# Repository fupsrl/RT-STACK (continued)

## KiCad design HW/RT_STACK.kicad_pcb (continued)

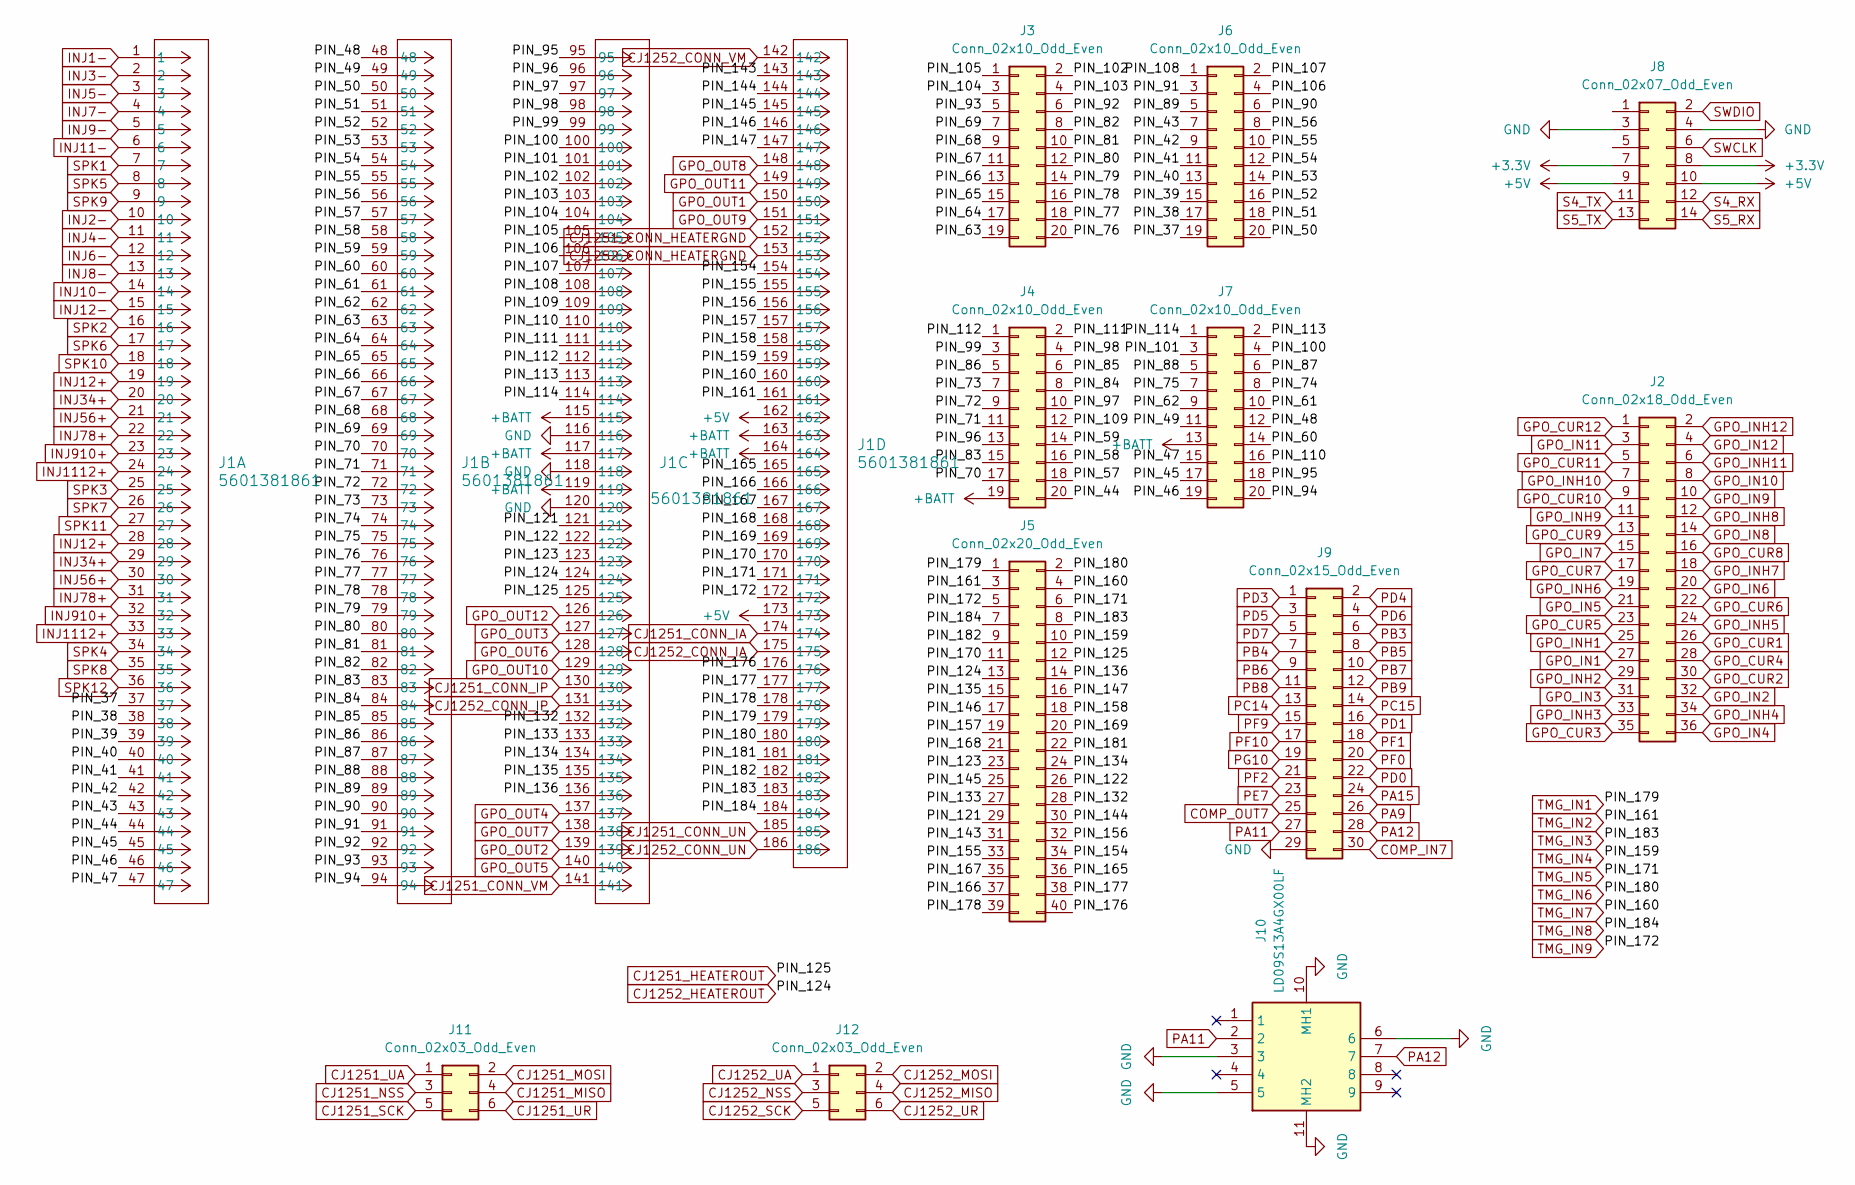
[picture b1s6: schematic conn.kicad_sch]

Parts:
J1: 5601381861; CONN_5601380001-SD_MOL
J2: Conn_02x18_Odd_Even; PinSocket_2x18_P2.54mm_Vertical_SMD
J3, J4, J6, J7: Conn_02x10_Odd_Even; PinSocket_2x10_P2.54mm_Vertical
J5: Conn_02x20_Odd_Even; PinSocket_2x20_P2.54mm_Vertical
J8: Conn_02x07_Odd_Even; IDC-Header_2x07_P2.54mm_Vertical
J9: Conn_02x15_Odd_Even; PinSocket_2x15_P2.54mm_Vertical
J10: LD09S13A4GX00LF; Manufacturer_Part_Number LD09S13A4GX00LF
J11, J12: Conn_02x03_Odd_Even; PinSocket_2x03_P2.54mm_Vertical_SMD

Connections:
+3.3V: J8.7, J8.8; also elsewhere on the board
+5V: J1.162, J1.173, J8.9, J8.10; also elsewhere on the board
+BATT: J1.115, J1.117, J1.119, J1.163, J1.164, J4.19, J7.13; also elsewhere on the board
/Connectors/PIN_37: J1.37, J6.19
/Connectors/PIN_38: J1.38, J6.17
/Connectors/PIN_39: J1.39, J6.15
/Connectors/PIN_40: J1.40, J6.13
/Connectors/PIN_41: J1.41, J6.11
/Connectors/PIN_42: J1.42, J6.9
/Connectors/PIN_43: J1.43, J6.7
/Connectors/PIN_44: J1.44, J4.20
/Connectors/PIN_45: J1.45, J7.17
/Connectors/PIN_46: J1.46, J7.19
/Connectors/PIN_47: J1.47, J7.15
/Connectors/PIN_48: J1.48, J7.12
/Connectors/PIN_49: J1.49, J7.11
/Connectors/PIN_50: J1.50, J6.20
/Connectors/PIN_51: J1.51, J6.18
/Connectors/PIN_52: J1.52, J6.16
/Connectors/PIN_53: J1.53, J6.14
/Connectors/PIN_54: J1.54, J6.12
/Connectors/PIN_55: J1.55, J6.10
/Connectors/PIN_56: J1.56, J6.8
/Connectors/PIN_57: J1.57, J4.18
/Connectors/PIN_58: J1.58, J4.16
/Connectors/PIN_59: J1.59, J4.14
/Connectors/PIN_60: J1.60, J7.14
/Connectors/PIN_61: J1.61, J7.10
/Connectors/PIN_62: J1.62, J7.9
/Connectors/PIN_63: J1.63, J3.19
/Connectors/PIN_64: J1.64, J3.17
/Connectors/PIN_65: J1.65, J3.15
/Connectors/PIN_66: J1.66, J3.13
/Connectors/PIN_67: J1.67, J3.11
/Connectors/PIN_68: J1.68, J3.9
/Connectors/PIN_69: J1.69, J3.7
/Connectors/PIN_70: J1.70, J4.17
/Connectors/PIN_71: J1.71, J4.11
/Connectors/PIN_72: J1.72, J4.9
/Connectors/PIN_73: J1.73, J4.7
/Connectors/PIN_74: J1.74, J7.8
/Connectors/PIN_75: J1.75, J7.7
/Connectors/PIN_76: J1.76, J3.20
/Connectors/PIN_77: J1.77, J3.18
/Connectors/PIN_78: J1.78, J3.16
/Connectors/PIN_79: J1.79, J3.14
/Connectors/PIN_80: J1.80, J3.12
/Connectors/PIN_81: J1.81, J3.10
/Connectors/PIN_82: J1.82, J3.8
/Connectors/PIN_83: J1.83, J4.15
/Connectors/PIN_84: J1.84, J4.8
/Connectors/PIN_85: J1.85, J4.6
/Connectors/PIN_86: J1.86, J4.5
/Connectors/PIN_87: J1.87, J7.6
/Connectors/PIN_88: J1.88, J7.5
/Connectors/PIN_89: J1.89, J6.5
/Connectors/PIN_90: J1.90, J6.6
/Connectors/PIN_91: J1.91, J6.3
/Connectors/PIN_92: J1.92, J3.6
/Connectors/PIN_93: J1.93, J3.5
/Connectors/PIN_94: J1.94, J7.20
/Connectors/PIN_95: J1.95, J7.18
/Connectors/PIN_96: J1.96, J4.13
/Connectors/PIN_97: J1.97, J4.10
/Connectors/PIN_98: J1.98, J4.4
/Connectors/PIN_99: J1.99, J4.3
/Connectors/PIN_100: J1.100, J7.4
/Connectors/PIN_101: J1.101, J7.3
/Connectors/PIN_102: J1.102, J3.2
/Connectors/PIN_103: J1.103, J3.4
/Connectors/PIN_104: J1.104, J3.3
/Connectors/PIN_105: J1.105, J3.1
/Connectors/PIN_106: J1.106, J6.4
/Connectors/PIN_107: J1.107, J6.2
/Connectors/PIN_108: J1.108, J6.1
/Connectors/PIN_109: J1.109, J4.12
/Connectors/PIN_110: J1.110, J7.16
/Connectors/PIN_111: J1.111, J4.2
/Connectors/PIN_112: J1.112, J4.1
/Connectors/PIN_113: J1.113, J7.2
/Connectors/PIN_114: J1.114, J7.1
/Connectors/PIN_121: J1.121, J5.29
/Connectors/PIN_122: J1.122, J5.26
/Connectors/PIN_123: J1.123, J5.23
/Connectors/PIN_132: J1.132, J5.28
/Connectors/PIN_133: J1.133, J5.27
/Connectors/PIN_134: J1.134, J5.24
/Connectors/PIN_135: J1.135, J5.15
/Connectors/PIN_136: J1.136, J5.14
/Connectors/PIN_143: J1.143, J5.31
/Connectors/PIN_144: J1.144, J5.30
/Connectors/PIN_145: J1.145, J5.25
/Connectors/PIN_146: J1.146, J5.17
/Connectors/PIN_147: J1.147, J5.16
/Connectors/PIN_154: J1.154, J5.34
/Connectors/PIN_155: J1.155, J5.33
/Connectors/PIN_156: J1.156, J5.32
/Connectors/PIN_157: J1.157, J5.19
/Connectors/PIN_158: J1.158, J5.18
/Connectors/PIN_165: J1.165, J5.36
/Connectors/PIN_166: J1.166, J5.37
/Connectors/PIN_167: J1.167, J5.35
/Connectors/PIN_168: J1.168, J5.21
/Connectors/PIN_169: J1.169, J5.20
/Connectors/PIN_170: J1.170, J5.11
/Connectors/PIN_176: J1.176, J5.40
/Connectors/PIN_177: J1.177, J5.38
/Connectors/PIN_178: J1.178, J5.39
/Connectors/PIN_181: J1.181, J5.22
/Connectors/PIN_182: J1.182, J5.9
CAN1_H: J9.28, J10.7; also elsewhere on the board
CAN1_L: J9.27, J10.2; also elsewhere on the board
CJ1251_CONN_HEATERGND: J1.152; also elsewhere on the board
CJ1251_CONN_IA: J1.174; also elsewhere on the board
CJ1251_CONN_IP: J1.130; also elsewhere on the board
CJ1251_CONN_UN: J1.185; also elsewhere on the board
CJ1251_CONN_VM: J1.141; also elsewhere on the board
CJ1251_HEATEROUT: J1.125, J5.12; also elsewhere on the board
CJ1251_MISO: J11.4; also elsewhere on the board
CJ1251_MOSI: J11.2; also elsewhere on the board
CJ1251_NSS: J11.3; also elsewhere on the board
CJ1251_SCK: J11.5; also elsewhere on the board
CJ1251_UA: J11.1; also elsewhere on the board
CJ1251_UR: J11.6; also elsewhere on the board
CJ1252_CONN_HEATERGND: J1.153; also elsewhere on the board
CJ1252_CONN_IA: J1.175; also elsewhere on the board
CJ1252_CONN_IP: J1.131; also elsewhere on the board
CJ1252_CONN_UN: J1.186; also elsewhere on the board
CJ1252_CONN_VM: J1.142; also elsewhere on the board
CJ1252_HEATEROUT: J1.124, J5.13; also elsewhere on the board
CJ1252_MISO: J12.4; also elsewhere on the board
CJ1252_MOSI: J12.2; also elsewhere on the board
CJ1252_NSS: J12.3; also elsewhere on the board
CJ1252_SCK: J12.5; also elsewhere on the board
CJ1252_UA: J12.1; also elsewhere on the board
CJ1252_UR: J12.6; also elsewhere on the board
COMP_IN7: J9.30; also elsewhere on the board
COMP_OUT7: J9.25; also elsewhere on the board
GND: J1.116, J1.118, J1.120, J8.3, J8.4, J9.29, J10.3, J10.5, J10.6, J10.10 (MH1), J10.11 (MH2); also elsewhere on the board
GPO_CUR1: J2.26; also elsewhere on the board
GPO_CUR2: J2.30; also elsewhere on the board
GPO_CUR3: J2.35; also elsewhere on the board
GPO_CUR4: J2.28; also elsewhere on the board
GPO_CUR5: J2.23; also elsewhere on the board
GPO_CUR6: J2.22; also elsewhere on the board
GPO_CUR7: J2.17; also elsewhere on the board
GPO_CUR8: J2.16; also elsewhere on the board
GPO_CUR9: J2.13; also elsewhere on the board
GPO_CUR10: J2.9; also elsewhere on the board
GPO_CUR11: J2.5; also elsewhere on the board
GPO_CUR12: J2.1; also elsewhere on the board
GPO_IN1: J2.27; also elsewhere on the board
GPO_IN2: J2.32; also elsewhere on the board
GPO_IN3: J2.31; also elsewhere on the board
GPO_IN4: J2.36; also elsewhere on the board
GPO_IN5: J2.21; also elsewhere on the board
GPO_IN6: J2.20; also elsewhere on the board
GPO_IN7: J2.15; also elsewhere on the board
GPO_IN8: J2.14; also elsewhere on the board
GPO_IN9: J2.10; also elsewhere on the board
GPO_IN10: J2.8; also elsewhere on the board
GPO_IN11: J2.3; also elsewhere on the board
GPO_IN12: J2.4; also elsewhere on the board
GPO_INH1: J2.25; also elsewhere on the board
GPO_INH2: J2.29; also elsewhere on the board
GPO_INH3: J2.33; also elsewhere on the board
GPO_INH4: J2.34; also elsewhere on the board
GPO_INH5: J2.24; also elsewhere on the board
GPO_INH6: J2.19; also elsewhere on the board
GPO_INH7: J2.18; also elsewhere on the board
GPO_INH8: J2.12; also elsewhere on the board
GPO_INH9: J2.11; also elsewhere on the board
GPO_INH10: J2.7; also elsewhere on the board
GPO_INH11: J2.6; also elsewhere on the board
GPO_INH12: J2.2; also elsewhere on the board
GPO_OUT1: J1.150; also elsewhere on the board
GPO_OUT2: J1.139; also elsewhere on the board
GPO_OUT3: J1.127; also elsewhere on the board
GPO_OUT4: J1.137; also elsewhere on the board
GPO_OUT5: J1.140; also elsewhere on the board
GPO_OUT6: J1.128; also elsewhere on the board
GPO_OUT7: J1.138; also elsewhere on the board
GPO_OUT8: J1.148; also elsewhere on the board
GPO_OUT9: J1.151; also elsewhere on the board
GPO_OUT10: J1.129; also elsewhere on the board
GPO_OUT11: J1.149; also elsewhere on the board
GPO_OUT12: J1.126; also elsewhere on the board
INJ1-: J1.1; also elsewhere on the board
INJ2-: J1.10; also elsewhere on the board
INJ3-: J1.2; also elsewhere on the board
INJ4-: J1.11; also elsewhere on the board
INJ5-: J1.3; also elsewhere on the board
INJ6-: J1.12; also elsewhere on the board
INJ7-: J1.4; also elsewhere on the board
INJ8-: J1.13; also elsewhere on the board
INJ9-: J1.5; also elsewhere on the board
INJ10-: J1.14; also elsewhere on the board
INJ11-: J1.6; also elsewhere on the board
INJ12+: J1.19, J1.28; also elsewhere on the board
INJ12-: J1.15; also elsewhere on the board
INJ34+: J1.20, J1.29; also elsewhere on the board
INJ56+: J1.21, J1.30; also elsewhere on the board
INJ78+: J1.22, J1.31; also elsewhere on the board
INJ910+: J1.23, J1.32; also elsewhere on the board
INJ1112+: J1.24, J1.33; also elsewhere on the board
PA9: J9.26; also elsewhere on the board
PA15: J9.24; also elsewhere on the board
PB3: J9.6; also elsewhere on the board
PB4: J9.7; also elsewhere on the board
PB5: J9.8; also elsewhere on the board
PB6: J9.9; also elsewhere on the board
PB7: J9.10; also elsewhere on the board
PB8: J9.11; also elsewhere on the board
PB9: J9.12; also elsewhere on the board
PC14: J9.13; also elsewhere on the board
PC15: J9.14; also elsewhere on the board
PD0: J9.22; also elsewhere on the board
PD1: J9.16; also elsewhere on the board
PD3: J9.1; also elsewhere on the board
PD4: J9.2; also elsewhere on the board
PD5: J9.3; also elsewhere on the board
PD6: J9.4; also elsewhere on the board
PD7: J9.5; also elsewhere on the board
PE7: J9.23; also elsewhere on the board
PF0: J9.20; also elsewhere on the board
PF1: J9.18; also elsewhere on the board
PF2: J9.21; also elsewhere on the board
PF9: J9.15; also elsewhere on the board
PF10: J9.17; also elsewhere on the board
PG10: J9.19; also elsewhere on the board
S4_RX: J8.12; also elsewhere on the board
S4_TX: J8.11; also elsewhere on the board
S5_RX: J8.14; also elsewhere on the board
S5_TX: J8.13; also elsewhere on the board
SPK1: J1.7; also elsewhere on the board
SPK2: J1.16; also elsewhere on the board
SPK3: J1.25; also elsewhere on the board
SPK4: J1.34; also elsewhere on the board
SPK5: J1.8; also elsewhere on the board
SPK6: J1.17; also elsewhere on the board
SPK7: J1.26; also elsewhere on the board
SPK8: J1.35; also elsewhere on the board
SPK9: J1.9; also elsewhere on the board
SPK10: J1.18; also elsewhere on the board
SPK11: J1.27; also elsewhere on the board
SPK12: J1.36; also elsewhere on the board
SWCLK: J8.6; also elsewhere on the board
SWDIO: J8.2; also elsewhere on the board
TMG_IN1: J1.179, J5.1; also elsewhere on the board
TMG_IN2: J1.161, J5.3; also elsewhere on the board
TMG_IN3: J1.183, J5.8; also elsewhere on the board
TMG_IN4: J1.159, J5.10; also elsewhere on the board
TMG_IN5: J1.171, J5.6; also elsewhere on the board
TMG_IN6: J1.180, J5.2; also elsewhere on the board
TMG_IN7: J1.160, J5.4; also elsewhere on the board
TMG_IN8: J1.184, J5.7; also elsewhere on the board
TMG_IN9: J1.172, J5.5; also elsewhere on the board

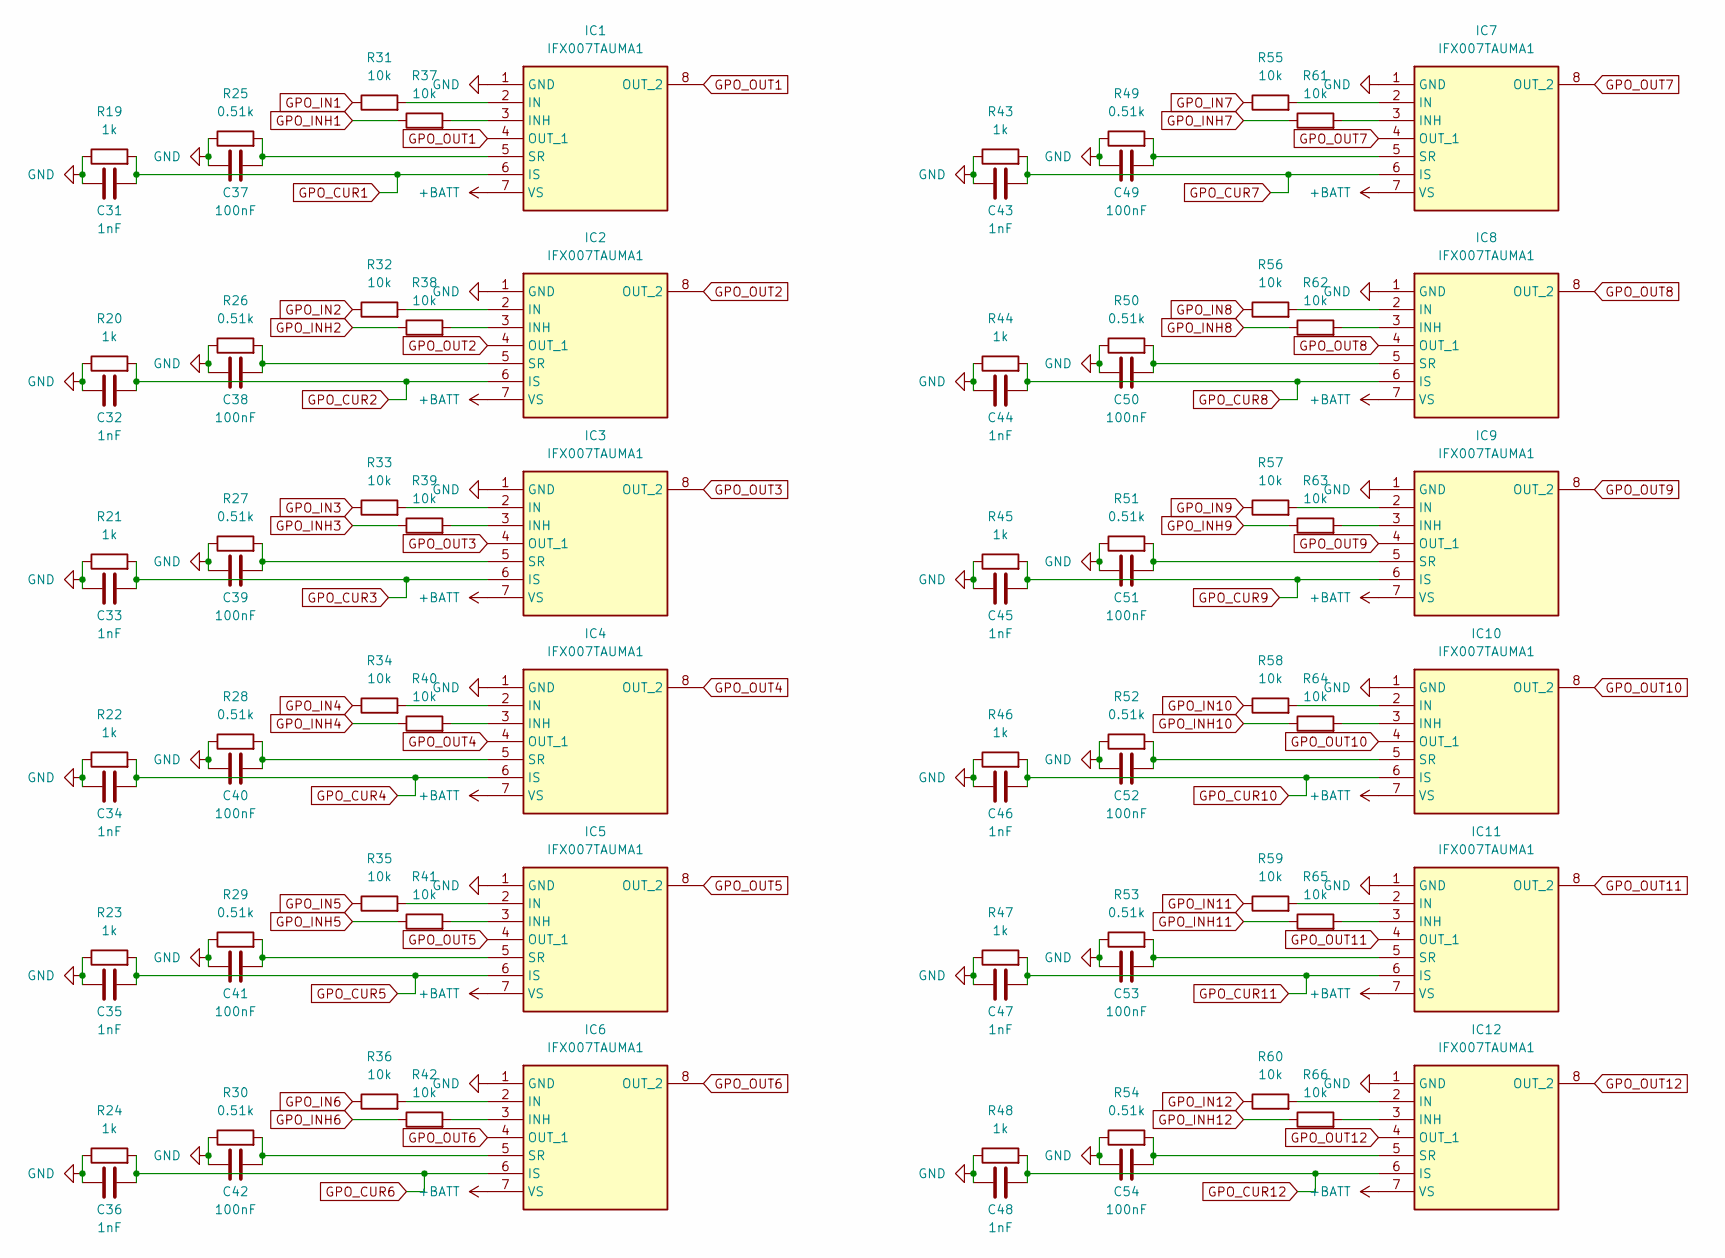
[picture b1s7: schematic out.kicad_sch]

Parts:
C31, C32, C33, C34, C35, C36, C43, C44, C45, C46, C47, C48: 1nF; C_0402_1005Metric
C37, C38, C39, C40, C41, C42, C49, C50, C51, C52, C53, C54: 100nF; C_0402_1005Metric
IC1, IC2, IC3, IC4, IC5, IC6, IC7, IC8, IC9, IC10, IC11, IC12: IFX007TAUMA1; PG-TO263-7-1; Mouser Part Number 726-IFX007TAUMA1
R19, R20, R21, R22, R23, R24, R43, R44, R45, R46, R47, R48: 1k; R_0402_1005Metric
R25, R26, R27, R28, R29, R30, R49, R50, R51, R52, R53, R54: 0.51k; R_0402_1005Metric
R31, R32, R33, R34, R35, R36, R37, R38, R39, R40, R41, R42, R55, R56, R57, R58, R59, R60, R61, R62, R63, R64, R65, R66: 10k; R_0402_1005Metric

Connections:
+BATT: IC1.7 (VS), IC2.7 (VS), IC3.7 (VS), IC4.7 (VS), IC5.7 (VS), IC6.7 (VS), IC7.7 (VS), IC8.7 (VS), IC9.7 (VS), IC10.7 (VS), IC11.7 (VS), IC12.7 (VS); also elsewhere on the board
GND: C31.1, C32.1, C33.1, C34.1, C35.1, C36.1, C37.1, C38.1, C39.1, C40.1, C41.1, C42.1, C43.1, C44.1, C45.1, C46.1, C47.1, C48.1, C49.1, C50.1, C51.1, C52.1, C53.1, C54.1, IC1.1 (GND), IC2.1 (GND), IC3.1 (GND), IC4.1 (GND), IC5.1 (GND), IC6.1 (GND), IC7.1 (GND), IC8.1 (GND), IC9.1 (GND), IC10.1 (GND), IC11.1 (GND), IC12.1 (GND), R19.1, R20.1, R21.1, R22.1, R23.1, R24.1, R25.1, R26.1, R27.1, R28.1, R29.1, R30.1, R43.1, R44.1, R45.1, R46.1, R47.1, R48.1, R49.1, R50.1, R51.1, R52.1, R53.1, R54.1; also elsewhere on the board
GPO_CUR1: C31.2, IC1.6 (IS), R19.2; also elsewhere on the board
GPO_CUR2: C32.2, IC2.6 (IS), R20.2; also elsewhere on the board
GPO_CUR3: C33.2, IC3.6 (IS), R21.2; also elsewhere on the board
GPO_CUR4: C34.2, IC4.6 (IS), R22.2; also elsewhere on the board
GPO_CUR5: C35.2, IC5.6 (IS), R23.2; also elsewhere on the board
GPO_CUR6: C36.2, IC6.6 (IS), R24.2; also elsewhere on the board
GPO_CUR7: C43.2, IC7.6 (IS), R43.2; also elsewhere on the board
GPO_CUR8: C44.2, IC8.6 (IS), R44.2; also elsewhere on the board
GPO_CUR9: C45.2, IC9.6 (IS), R45.2; also elsewhere on the board
GPO_CUR10: C46.2, IC10.6 (IS), R46.2; also elsewhere on the board
GPO_CUR11: C47.2, IC11.6 (IS), R47.2; also elsewhere on the board
GPO_CUR12: C48.2, IC12.6 (IS), R48.2; also elsewhere on the board
GPO_IN1: R31.1; also elsewhere on the board
GPO_IN2: R32.1; also elsewhere on the board
GPO_IN3: R33.1; also elsewhere on the board
GPO_IN4: R34.1; also elsewhere on the board
GPO_IN5: R35.1; also elsewhere on the board
GPO_IN6: R36.1; also elsewhere on the board
GPO_IN7: R55.1; also elsewhere on the board
GPO_IN8: R56.1; also elsewhere on the board
GPO_IN9: R57.1; also elsewhere on the board
GPO_IN10: R58.1; also elsewhere on the board
GPO_IN11: R59.1; also elsewhere on the board
GPO_IN12: R60.1; also elsewhere on the board
GPO_INH1: R37.1; also elsewhere on the board
GPO_INH2: R38.1; also elsewhere on the board
GPO_INH3: R39.1; also elsewhere on the board
GPO_INH4: R40.1; also elsewhere on the board
GPO_INH5: R41.1; also elsewhere on the board
GPO_INH6: R42.1; also elsewhere on the board
GPO_INH7: R61.1; also elsewhere on the board
GPO_INH8: R62.1; also elsewhere on the board
GPO_INH9: R63.1; also elsewhere on the board
GPO_INH10: R64.1; also elsewhere on the board
GPO_INH11: R65.1; also elsewhere on the board
GPO_INH12: R66.1; also elsewhere on the board
GPO_OUT1: IC1.4 (OUT_1), IC1.8 (OUT_2); also elsewhere on the board
GPO_OUT2: IC2.4 (OUT_1), IC2.8 (OUT_2); also elsewhere on the board
GPO_OUT3: IC3.4 (OUT_1), IC3.8 (OUT_2); also elsewhere on the board
GPO_OUT4: IC4.4 (OUT_1), IC4.8 (OUT_2); also elsewhere on the board
GPO_OUT5: IC5.4 (OUT_1), IC5.8 (OUT_2); also elsewhere on the board
GPO_OUT6: IC6.4 (OUT_1), IC6.8 (OUT_2); also elsewhere on the board
GPO_OUT7: IC7.4 (OUT_1), IC7.8 (OUT_2); also elsewhere on the board
GPO_OUT8: IC8.4 (OUT_1), IC8.8 (OUT_2); also elsewhere on the board
GPO_OUT9: IC9.4 (OUT_1), IC9.8 (OUT_2); also elsewhere on the board
GPO_OUT10: IC10.4 (OUT_1), IC10.8 (OUT_2); also elsewhere on the board
GPO_OUT11: IC11.4 (OUT_1), IC11.8 (OUT_2); also elsewhere on the board
GPO_OUT12: IC12.4 (OUT_1), IC12.8 (OUT_2); also elsewhere on the board
unnamed: IC1.2 (IN), R31.2
unnamed: IC1.3 (INH), R37.2
unnamed: C37.2, IC1.5 (SR), R25.2
unnamed: IC2.2 (IN), R32.2
unnamed: IC2.3 (INH), R38.2
unnamed: C38.2, IC2.5 (SR), R26.2
unnamed: IC3.2 (IN), R33.2
unnamed: IC3.3 (INH), R39.2
unnamed: C39.2, IC3.5 (SR), R27.2
unnamed: IC4.2 (IN), R34.2
unnamed: IC4.3 (INH), R40.2
unnamed: C40.2, IC4.5 (SR), R28.2
unnamed: IC5.2 (IN), R35.2
unnamed: IC5.3 (INH), R41.2
unnamed: C41.2, IC5.5 (SR), R29.2
unnamed: IC6.2 (IN), R36.2
unnamed: IC6.3 (INH), R42.2
unnamed: C42.2, IC6.5 (SR), R30.2
unnamed: IC7.2 (IN), R55.2
unnamed: IC7.3 (INH), R61.2
unnamed: C49.2, IC7.5 (SR), R49.2
unnamed: IC8.2 (IN), R56.2
unnamed: IC8.3 (INH), R62.2
unnamed: C50.2, IC8.5 (SR), R50.2
unnamed: IC9.2 (IN), R57.2
unnamed: IC9.3 (INH), R63.2
unnamed: C51.2, IC9.5 (SR), R51.2
unnamed: IC10.2 (IN), R58.2
unnamed: IC10.3 (INH), R64.2
unnamed: C52.2, IC10.5 (SR), R52.2
unnamed: IC11.2 (IN), R59.2
unnamed: IC11.3 (INH), R65.2
unnamed: C53.2, IC11.5 (SR), R53.2
unnamed: IC12.2 (IN), R60.2
unnamed: IC12.3 (INH), R66.2
unnamed: C54.2, IC12.5 (SR), R54.2

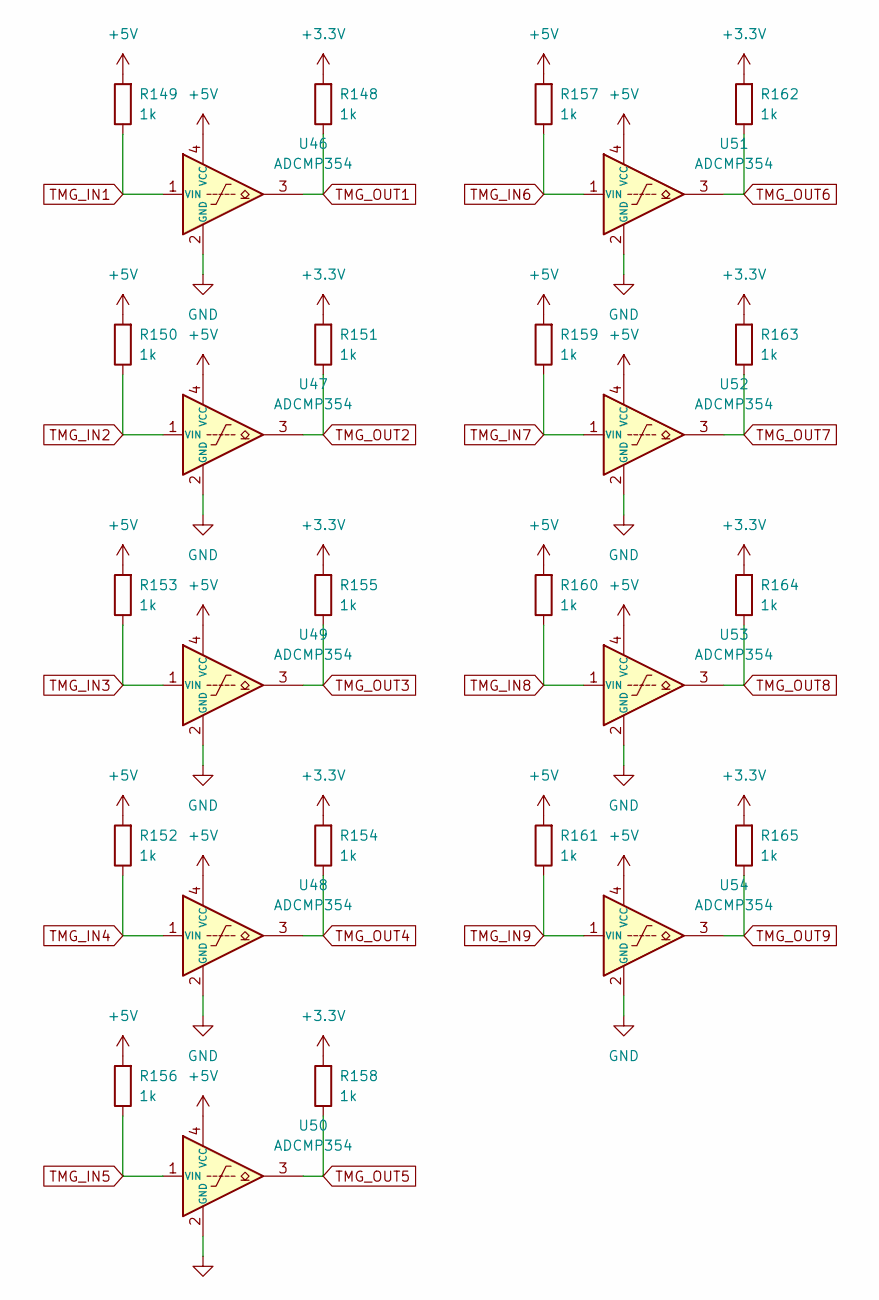
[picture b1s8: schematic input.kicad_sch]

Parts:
R148, R151, R154, R155, R158, R162, R163, R164, R165: 1k; R_0402_1005Metric
R149, R150, R152, R153, R156, R157, R159, R160, R161: 1k; R_Axial_DIN0204_L3.6mm_D1.6mm_P1.90mm_Vertical
U46, U47, U48, U49, U50, U51, U52, U53, U54: ADCMP354; Analog_KS-4

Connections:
+3.3V: R148.2, R151.2, R154.2, R155.2, R158.2, R162.2, R163.2, R164.2, R165.2; also elsewhere on the board
+5V: R149.2, R150.2, R152.2, R153.2, R156.2, R157.2, R159.2, R160.2, R161.2, U46.4 (VCC), U47.4 (VCC), U48.4 (VCC), U49.4 (VCC), U50.4 (VCC), U51.4 (VCC), U52.4 (VCC), U53.4 (VCC), U54.4 (VCC); also elsewhere on the board
GND: U46.2 (GND), U47.2 (GND), U48.2 (GND), U49.2 (GND), U50.2 (GND), U51.2 (GND), U52.2 (GND), U53.2 (GND), U54.2 (GND); also elsewhere on the board
TMG_IN1: R149.1, U46.1 (VIN); also elsewhere on the board
TMG_IN2: R150.1, U47.1 (VIN); also elsewhere on the board
TMG_IN3: R153.1, U49.1 (VIN); also elsewhere on the board
TMG_IN4: R152.1, U48.1 (VIN); also elsewhere on the board
TMG_IN5: R156.1, U50.1 (VIN); also elsewhere on the board
TMG_IN6: R157.1, U51.1 (VIN); also elsewhere on the board
TMG_IN7: R159.1, U52.1 (VIN); also elsewhere on the board
TMG_IN8: R160.1, U53.1 (VIN); also elsewhere on the board
TMG_IN9: R161.1, U54.1 (VIN); also elsewhere on the board
TMG_OUT1: R148.1, U46.3; also elsewhere on the board
TMG_OUT2: R151.1, U47.3; also elsewhere on the board
TMG_OUT3: R155.1, U49.3; also elsewhere on the board
TMG_OUT4: R154.1, U48.3; also elsewhere on the board
TMG_OUT5: R158.1, U50.3; also elsewhere on the board
TMG_OUT6: R162.1, U51.3; also elsewhere on the board
TMG_OUT7: R163.1, U52.3; also elsewhere on the board
TMG_OUT8: R164.1, U53.3; also elsewhere on the board
TMG_OUT9: R165.1, U54.3; also elsewhere on the board

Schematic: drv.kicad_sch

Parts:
C4, C5, C10, C11, C12: 100nF; C_0402_1005Metric
C6, C7: 1uF; C_0402_1005Metric
C8, C9: 10nF; C_0402_1005Metric
D1, D2: 1N4148WS; D_SOD-323; Forward Voltage (Vf@If) 1.25V@150mA; Reverse Voltage (Vr) 100V; Part 1N4148WS; LCSC C2128
D3, D4, D5, D6, D7, D8: SK520B; D_SMB; LCSC C139681
Q1, Q2, Q3, Q4, Q5, Q6: SUD80460E; TO-252-2
R1, R2: R0; R_0402_1005Metric
R3, R4, R5, R6: R10; R_0402_1005Metric
U19, U20: IR2101; SOIC-8_3.9x4.9mm_P1.27mm
U21, U22: ACS722xLCTR-20AB; SOIC-8_3.9x4.9mm_P1.27mm
U23: TC4427xOA; SOIC-8_3.9x4.9mm_P1.27mm; JLC C640788

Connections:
+3.3V: C10.1, C11.1, U21.8 (VCC), U22.8 (VCC); also elsewhere on the board
+BATT: C4.1, C5.1, C12.1, D1.2, D2.2, D5.2 (A), D6.2 (A), U19.1 (VCC), U20.1 (VCC), U23.6 (VDD); also elsewhere on the board
/Inj Drivers/GDI BANK 2/P1: C6.2, D5.1 (K), Q1.3 (S), U19.6 (VS), U21.3 (IP-), U21.4 (IP-)
/Inj Drivers/GDI BANK 2/P2: C7.2, D6.1 (K), Q3.3 (S), U20.6 (VS), U22.3 (IP-), U22.4 (IP-)
/Inj Drivers/INJ5_L: U19.3 (LIN); also elsewhere on the board
/Inj Drivers/INJ6_L: U23.4 (IN_B); also elsewhere on the board
/Inj Drivers/INJ7_L: U20.3 (LIN); also elsewhere on the board
/Inj Drivers/INJ8_L: U23.2 (IN_A); also elsewhere on the board
BOOST56: U19.2 (HIN); also elsewhere on the board
BOOST78: U20.2 (HIN); also elsewhere on the board
COMP_IN3: C8.1, U21.7 (VIOUT); also elsewhere on the board
COMP_IN4: C9.1, U22.7 (VIOUT); also elsewhere on the board
GND: C4.2, C5.2, C8.2, C9.2, C10.2, C11.2, C12.2, Q2.3 (S), Q4.3 (S), Q5.3 (S), Q6.3 (S), U19.4 (COM), U20.4 (COM), U21.5 (GND), U21.6 (BW_SEL), U22.5 (GND), U22.6 (BW_SEL), U23.3 (GND); also elsewhere on the board
INJ5-: D3.2 (A), Q2.2 (D); also elsewhere on the board
INJ6-: D7.2 (A), Q5.2 (D); also elsewhere on the board
INJ7-: D4.2 (A), Q4.2 (D); also elsewhere on the board
INJ8-: D8.2 (A), Q6.2 (D); also elsewhere on the board
INJ56+: U21.1 (IP+), U21.2 (IP+); also elsewhere on the board
INJ78+: U22.1 (IP+), U22.2 (IP+); also elsewhere on the board
unnamed: Q1.1 (G), R1.2
unnamed: Q2.1 (G), R3.2
unnamed: Q3.1 (G), R2.2
unnamed: Q4.1 (G), R4.1
unnamed: Q5.1 (G), R5.2
unnamed: Q6.1 (G), R6.2
unnamed: R1.1, U19.7 (HO)
unnamed: R3.1, U19.5 (LO)
unnamed: C6.1, D1.1, U19.8 (VB)
unnamed: R2.1, U20.7 (HO)
unnamed: R4.2, U20.5 (LO)
unnamed: C7.1, D2.1, U20.8 (VB)
unnamed: R6.1, U23.7 (OUT_A)
unnamed: R5.1, U23.5 (OUT_B)
VBUS: D3.1 (K), D4.1 (K), D7.1 (K), D8.1 (K), Q1.2 (D), Q3.2 (D); also elsewhere on the board

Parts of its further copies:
C13, C14, C19, C20, C21, C22, C23, C28, C29, C30: 100nF; C_0402_1005Metric
C15, C16, C24, C25: 1uF; C_0402_1005Metric
C17, C18, C26, C27: 10nF; C_0402_1005Metric
D9, D10, D17, D18: 1N4148WS; D_SOD-323; Forward Voltage (Vf@If) 1.25V@150mA; Reverse Voltage (Vr) 100V; Part 1N4148WS; LCSC C2128
D11, D12, D13, D14, D15, D16, D19, D20, D21, D22, D23, D24: SK520B; D_SMB; LCSC C139681
Q7, Q8, Q9, Q10, Q11, Q12, Q13, Q14, Q15, Q16, Q17, Q18: SUD80460E; TO-252-2
R7, R8, R13, R14: R0; R_0402_1005Metric
R9, R10, R11, R12, R15, R16, R17, R18: R10; R_0402_1005Metric
U24, U25, U29, U30: IR2101; SOIC-8_3.9x4.9mm_P1.27mm
U26, U27, U31, U32: ACS722xLCTR-20AB; SOIC-8_3.9x4.9mm_P1.27mm
U28, U33: TC4427xOA; SOIC-8_3.9x4.9mm_P1.27mm; JLC C640788

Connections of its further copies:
+3.3V: C19.1, C20.1, C28.1, C29.1, U26.8 (VCC), U27.8 (VCC), U31.8 (VCC), U32.8 (VCC); also elsewhere on the board
+BATT: C13.1, C14.1, C21.1, C22.1, C23.1, C30.1, D9.2, D10.2, D13.2 (A), D14.2 (A), D17.2, D18.2, D21.2 (A), D22.2 (A), U24.1 (VCC), U25.1 (VCC), U28.6 (VDD), U29.1 (VCC), U30.1 (VCC), U33.6 (VDD); also elsewhere on the board
/Inj Drivers/GDI BANK1/P1: C24.2, D21.1 (K), Q13.3 (S), U29.6 (VS), U31.3 (IP-), U31.4 (IP-)
/Inj Drivers/GDI BANK1/P2: C25.2, D22.1 (K), Q15.3 (S), U30.6 (VS), U32.3 (IP-), U32.4 (IP-)
/Inj Drivers/GDI BANK 3/P1: C15.2, D13.1 (K), Q7.3 (S), U24.6 (VS), U26.3 (IP-), U26.4 (IP-)
/Inj Drivers/GDI BANK 3/P2: C16.2, D14.1 (K), Q9.3 (S), U25.6 (VS), U27.3 (IP-), U27.4 (IP-)
/Inj Drivers/INJ1_L: U29.3 (LIN); also elsewhere on the board
/Inj Drivers/INJ2_L: U33.4 (IN_B); also elsewhere on the board
/Inj Drivers/INJ3_L: U30.3 (LIN); also elsewhere on the board
/Inj Drivers/INJ4_L: U33.2 (IN_A); also elsewhere on the board
/Inj Drivers/INJ9_L: U24.3 (LIN); also elsewhere on the board
/Inj Drivers/INJ10_L: U28.4 (IN_B); also elsewhere on the board
/Inj Drivers/INJ11_L: U25.3 (LIN); also elsewhere on the board
/Inj Drivers/INJ12_L: U28.2 (IN_A); also elsewhere on the board
BOOST12: U29.2 (HIN); also elsewhere on the board
BOOST34: U30.2 (HIN); also elsewhere on the board
BOOST910: U24.2 (HIN); also elsewhere on the board
BOOST1112: U25.2 (HIN); also elsewhere on the board
COMP_IN1: C26.1, U31.7 (VIOUT); also elsewhere on the board
COMP_IN2: C27.1, U32.7 (VIOUT); also elsewhere on the board
COMP_IN5: C17.1, U26.7 (VIOUT); also elsewhere on the board
COMP_IN6: C18.1, U27.7 (VIOUT); also elsewhere on the board
GND: C13.2, C14.2, C17.2, C18.2, C19.2, C20.2, C21.2, C22.2, C23.2, C26.2, C27.2, C28.2, C29.2, C30.2, Q8.3 (S), Q10.3 (S), Q11.3 (S), Q12.3 (S), Q14.3 (S), Q16.3 (S), Q17.3 (S), Q18.3 (S), U24.4 (COM), U25.4 (COM), U26.5 (GND), U26.6 (BW_SEL), U27.5 (GND), U27.6 (BW_SEL), U28.3 (GND), U29.4 (COM), U30.4 (COM), U31.5 (GND), U31.6 (BW_SEL), U32.5 (GND), U32.6 (BW_SEL), U33.3 (GND); also elsewhere on the board
INJ1-: D19.2 (A), Q14.2 (D); also elsewhere on the board
INJ2-: D23.2 (A), Q17.2 (D); also elsewhere on the board
INJ3-: D20.2 (A), Q16.2 (D); also elsewhere on the board
INJ4-: D24.2 (A), Q18.2 (D); also elsewhere on the board
INJ9-: D11.2 (A), Q8.2 (D); also elsewhere on the board
INJ10-: D15.2 (A), Q11.2 (D); also elsewhere on the board
INJ11-: D12.2 (A), Q10.2 (D); also elsewhere on the board
INJ12+: U31.1 (IP+), U31.2 (IP+); also elsewhere on the board
INJ12-: D16.2 (A), Q12.2 (D); also elsewhere on the board
INJ34+: U32.1 (IP+), U32.2 (IP+); also elsewhere on the board
INJ910+: U26.1 (IP+), U26.2 (IP+); also elsewhere on the board
INJ1112+: U27.1 (IP+), U27.2 (IP+); also elsewhere on the board
unnamed: Q7.1 (G), R7.2
unnamed: Q8.1 (G), R9.2
unnamed: Q9.1 (G), R8.2
unnamed: Q10.1 (G), R10.1
unnamed: Q11.1 (G), R11.2
unnamed: Q12.1 (G), R12.2
unnamed: Q13.1 (G), R13.2
unnamed: Q14.1 (G), R15.2
unnamed: Q15.1 (G), R14.2
unnamed: Q16.1 (G), R16.1
unnamed: Q17.1 (G), R17.2
unnamed: Q18.1 (G), R18.2
unnamed: R7.1, U24.7 (HO)
unnamed: R9.1, U24.5 (LO)
unnamed: C15.1, D9.1, U24.8 (VB)
unnamed: R8.1, U25.7 (HO)
unnamed: R10.2, U25.5 (LO)
unnamed: C16.1, D10.1, U25.8 (VB)
unnamed: R12.1, U28.7 (OUT_A)
unnamed: R11.1, U28.5 (OUT_B)
unnamed: R13.1, U29.7 (HO)
unnamed: R15.1, U29.5 (LO)
unnamed: C24.1, D17.1, U29.8 (VB)
unnamed: R14.1, U30.7 (HO)
unnamed: R16.2, U30.5 (LO)
unnamed: C25.1, D18.1, U30.8 (VB)
unnamed: R18.1, U33.7 (OUT_A)
unnamed: R17.1, U33.5 (OUT_B)
VBUS: D11.1 (K), D12.1 (K), D15.1 (K), D16.1 (K), D19.1 (K), D20.1 (K), D23.1 (K), D24.1 (K), Q7.2 (D), Q9.2 (D), Q13.2 (D), Q15.2 (D); also elsewhere on the board
